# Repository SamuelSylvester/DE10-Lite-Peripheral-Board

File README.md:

## DSD SHIELD

Folder to contain the DE10-Lite shield for ECE 4110/5110 development

Include all files, libraries, and documents.

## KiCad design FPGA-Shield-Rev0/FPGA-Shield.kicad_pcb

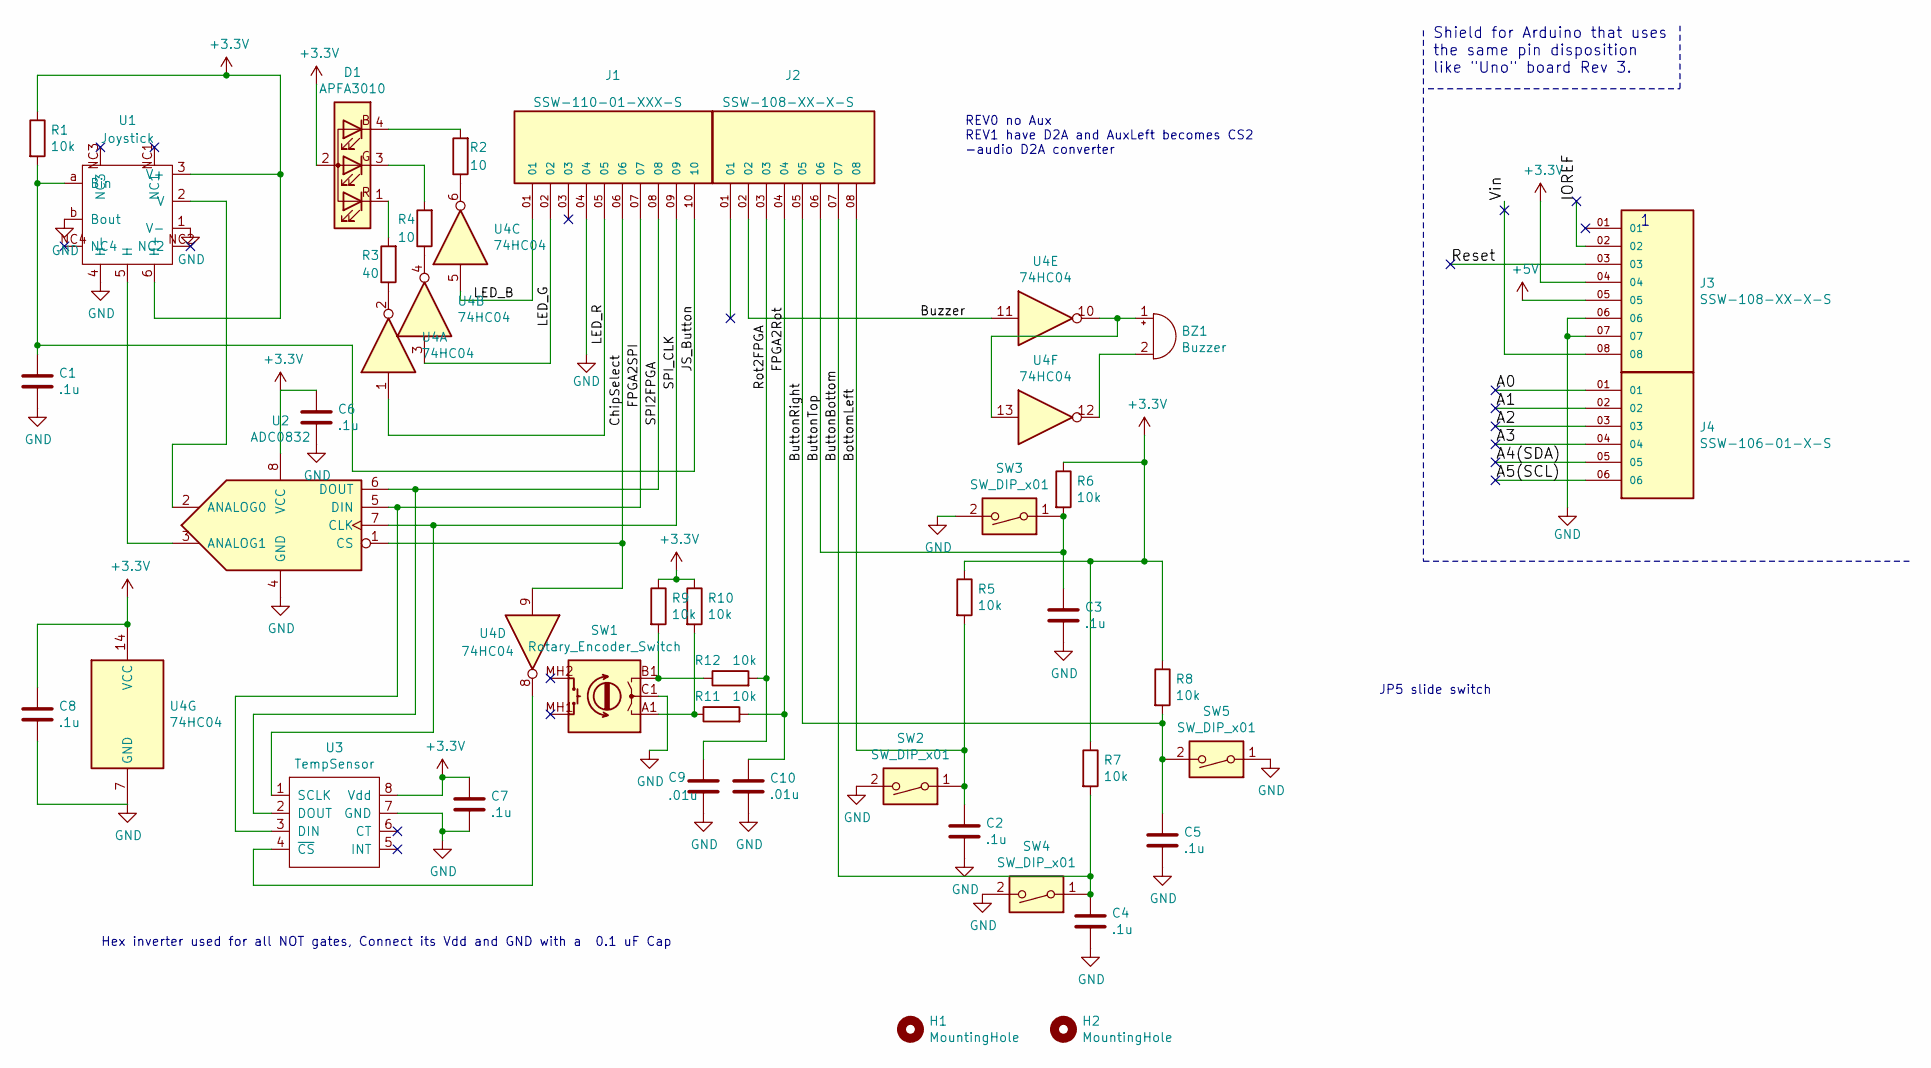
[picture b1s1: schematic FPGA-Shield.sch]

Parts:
BZ1: Buzzer; Buzzer_D14mm_H7mm_P10mm
C1, C2, C3, C4, C5, C6, C7, C8: .1u; C_1206_3216Metric_Pad1.33x1.80mm_HandSolder
C9, C10: .01u; C_1206_3216Metric_Pad1.33x1.80mm_HandSolder
D1: APFA3010; RGBLED-5218559F
H1, H2: MountingHole; MountingHole_2.5mm
J1: SSW-110-01-XXX-S; SAMTEC_SSW-110-01-XXX-S; PARTREV A
J2, J3: SSW-108-XX-X-S; SAMTEC_SSW-108-XX-X-S; PARTREV A
J4: SSW-106-01-X-S; SAMTEC_SSW-106-01-X-S; PARTREV A
R1, R5, R6, R7, R8, R9, R10, R11, R12: 10k; R_1206_3216Metric_Pad1.30x1.75mm_HandSolder
R2, R4: 10; R_1206_3216Metric_Pad1.30x1.75mm_HandSolder
R3: 40; R_1206_3216Metric_Pad1.30x1.75mm_HandSolder
SW1: Rotary_Encoder_Switch; RotaryEncoder-PEC12R4020FN0024
SW2, SW3, SW4, SW5: SW_DIP_x01; SW_PUSH_6mm_LargeHoles
U1: Joystick
U2: ADC0832; ADC-SOP65P490X110-8N
U3: TempSensor; TempSensor-SOIC127P600X175-8N
U4: 74HC04; HexInv-DIP794W53P254L1930H508Q14N

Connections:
+3V3: C6.1, C7.1, C8.1, D1.2 (A), J3.04, R1.1, R5.1, R6.1, R7.1, R8.1, R9.1, R10.1, U1.3 (V+), U1.6 (H+), U2.8 (VCC), U3.8 (Vdd), U4.14 (VCC)
+5V: J3.05
/A0: J4.01
/A1: J4.02
/A2: J4.03
/A3: J4.04
/A4(SDA): J4.05
/A5(SCL): J4.06
/BottomLeft: C2.1, J2.08, R5.2, SW2.1
/ButtonBottom: C4.1, J2.07, R7.2, SW4.1
/ButtonRight: C5.1, J2.05, R8.2, SW5.2
/ButtonTop: C3.1, J2.06, R6.2, SW3.1
/Buzzer: J2.02, U4.11
/ChipSelect: J1.06, U2.1 (CS), U4.9
/FPGA2Rot: C10.1, J2.04, R11.2
/FPGA2SPI: J1.07, U2.5 (DIN), U3.3 (DIN)
/IOREF: J3.02
/JS_Button: C1.1, J1.10, R1.2, U1.a (Bin)
/LED_B: J1.01, U4.5
/LED_G: J1.02, U4.3
/LED_R: J1.05, U4.1
/Reset: J3.03
/Rot2FPGA: C9.1, J2.03, R12.2
/SPI2FPGA: J1.08, U2.6 (DOUT), U3.2 (DOUT)
/SPI_CLK: J1.09, U2.7 (CLK), U3.1 (SCLK)
/Vin: J3.08
GND: C1.2, C2.2, C3.2, C4.2, C5.2, C6.2, C7.2, C8.2, C9.2, C10.2, J1.04, J3.06, J3.07, SW1.C1, SW2.2, SW3.2, SW4.2, SW5.1, U1.1 (V-), U1.4 (H-), U1.b (Bout), U2.4 (GND), U3.7 (GND), U4.7 (GND)
unnamed: BZ1.1 (-), U4.10, U4.13
unnamed: BZ1.2 (+), U4.12
unnamed: D1.1 (R), R3.2
unnamed: D1.3 (G), R4.2
unnamed: D1.4 (B), R2.2
unnamed: R2.1, U4.6
unnamed: R3.1, U4.2
unnamed: R4.1, U4.4
unnamed: R10.2, R11.1, SW1.A1
unnamed: R9.2, R12.1, SW1.B1
unnamed: U1.2 (V), U2.2 (ANALOG0)
unnamed: U1.5 (H), U2.3 (ANALOG1)
unnamed: U3.4 (~CS), U4.8

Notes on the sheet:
Shield for Arduino that uses the same pin disposition like "Uno" board Rev 3.
Hex inverter used for all NOT gates, Connect its Vdd and GND with a 0.1 uF Cap
JP5 slide switch
REV0 no Aux REV1 have D2A and AuxLeft becomes CS2 -audio D2A converter

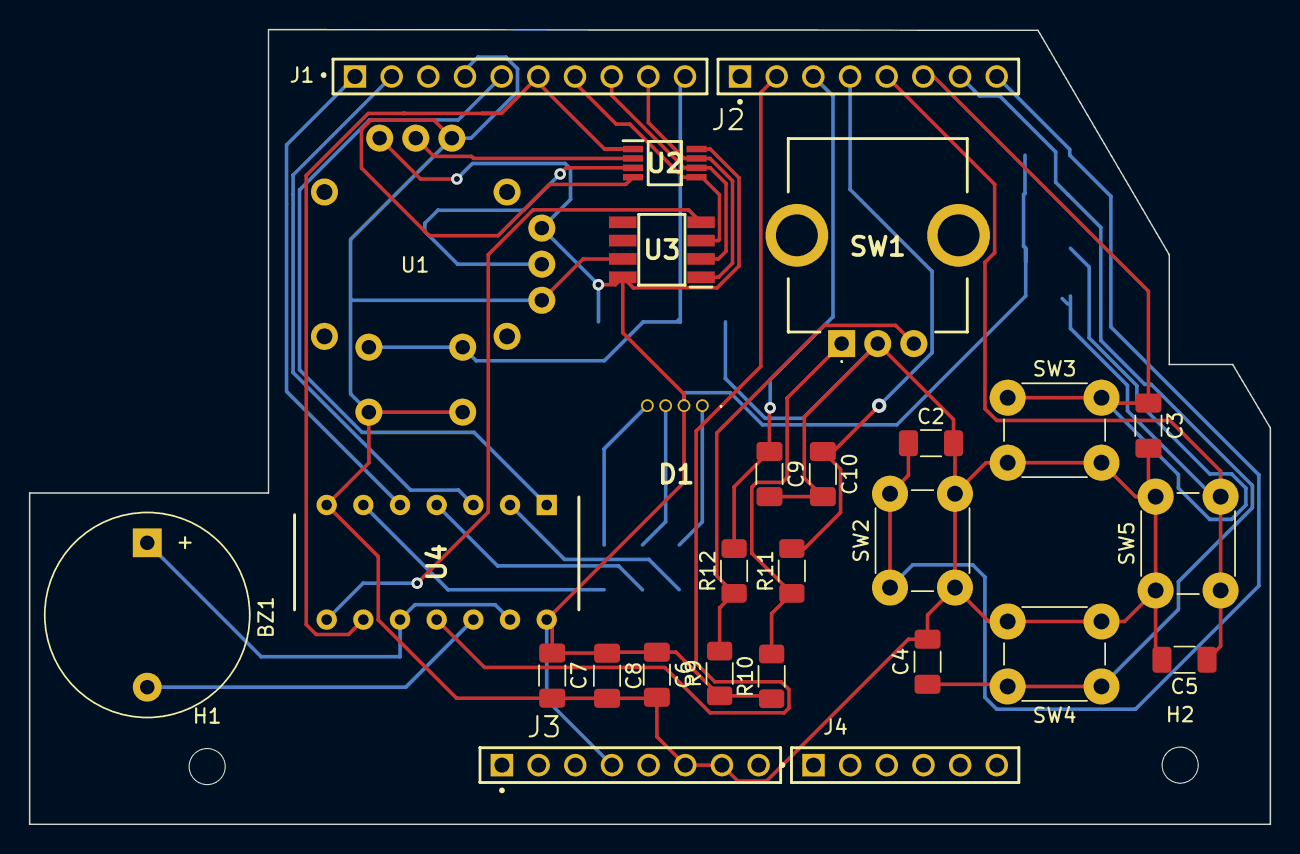
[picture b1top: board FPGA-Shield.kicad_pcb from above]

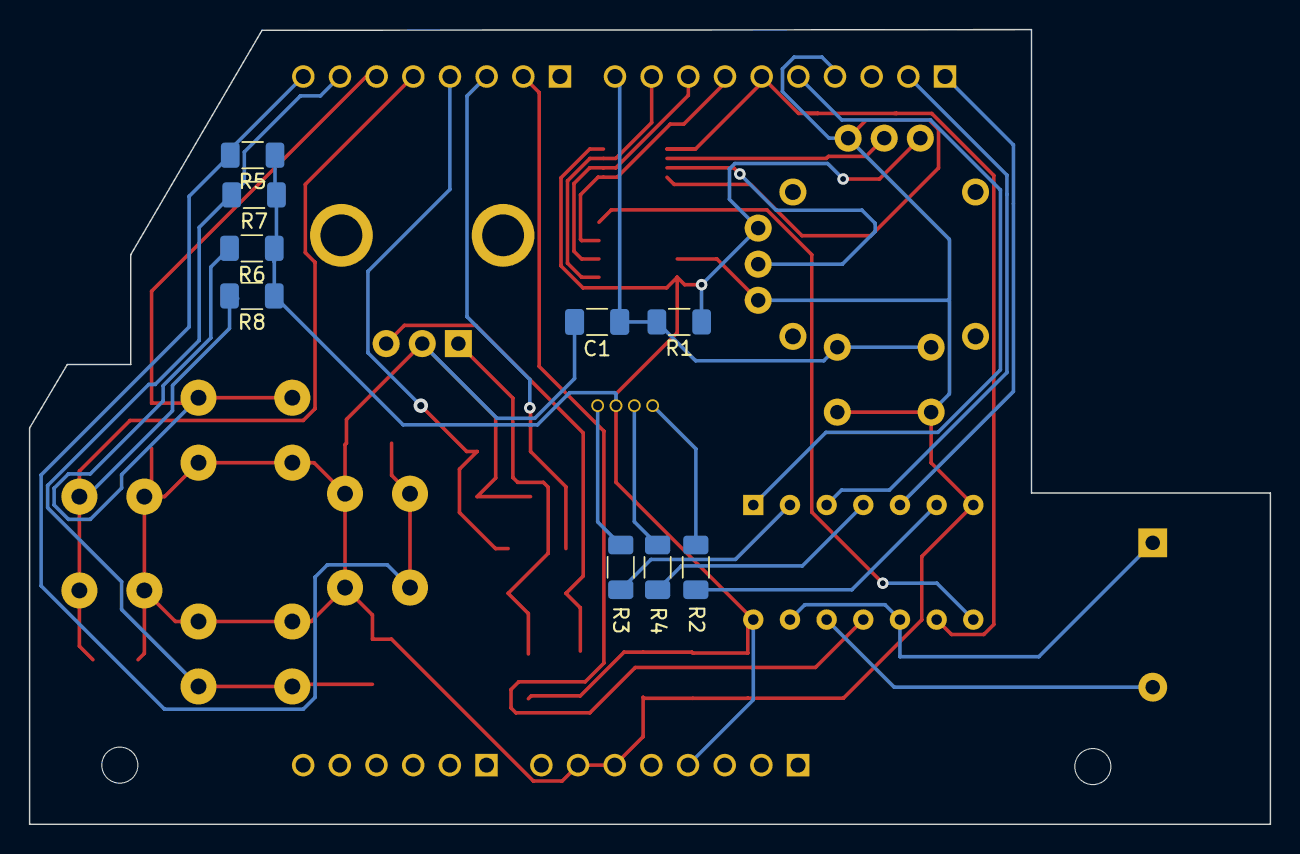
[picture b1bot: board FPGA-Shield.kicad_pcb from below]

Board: 2 copper layers, 85.9 x 55.0 mm, 39 parts (9 on the bottom side), 30 nets.

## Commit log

2024-01-12 commit
    initial design for a peripheral board for the DE10-Lite FPGA to be used in the ECE2110 class
